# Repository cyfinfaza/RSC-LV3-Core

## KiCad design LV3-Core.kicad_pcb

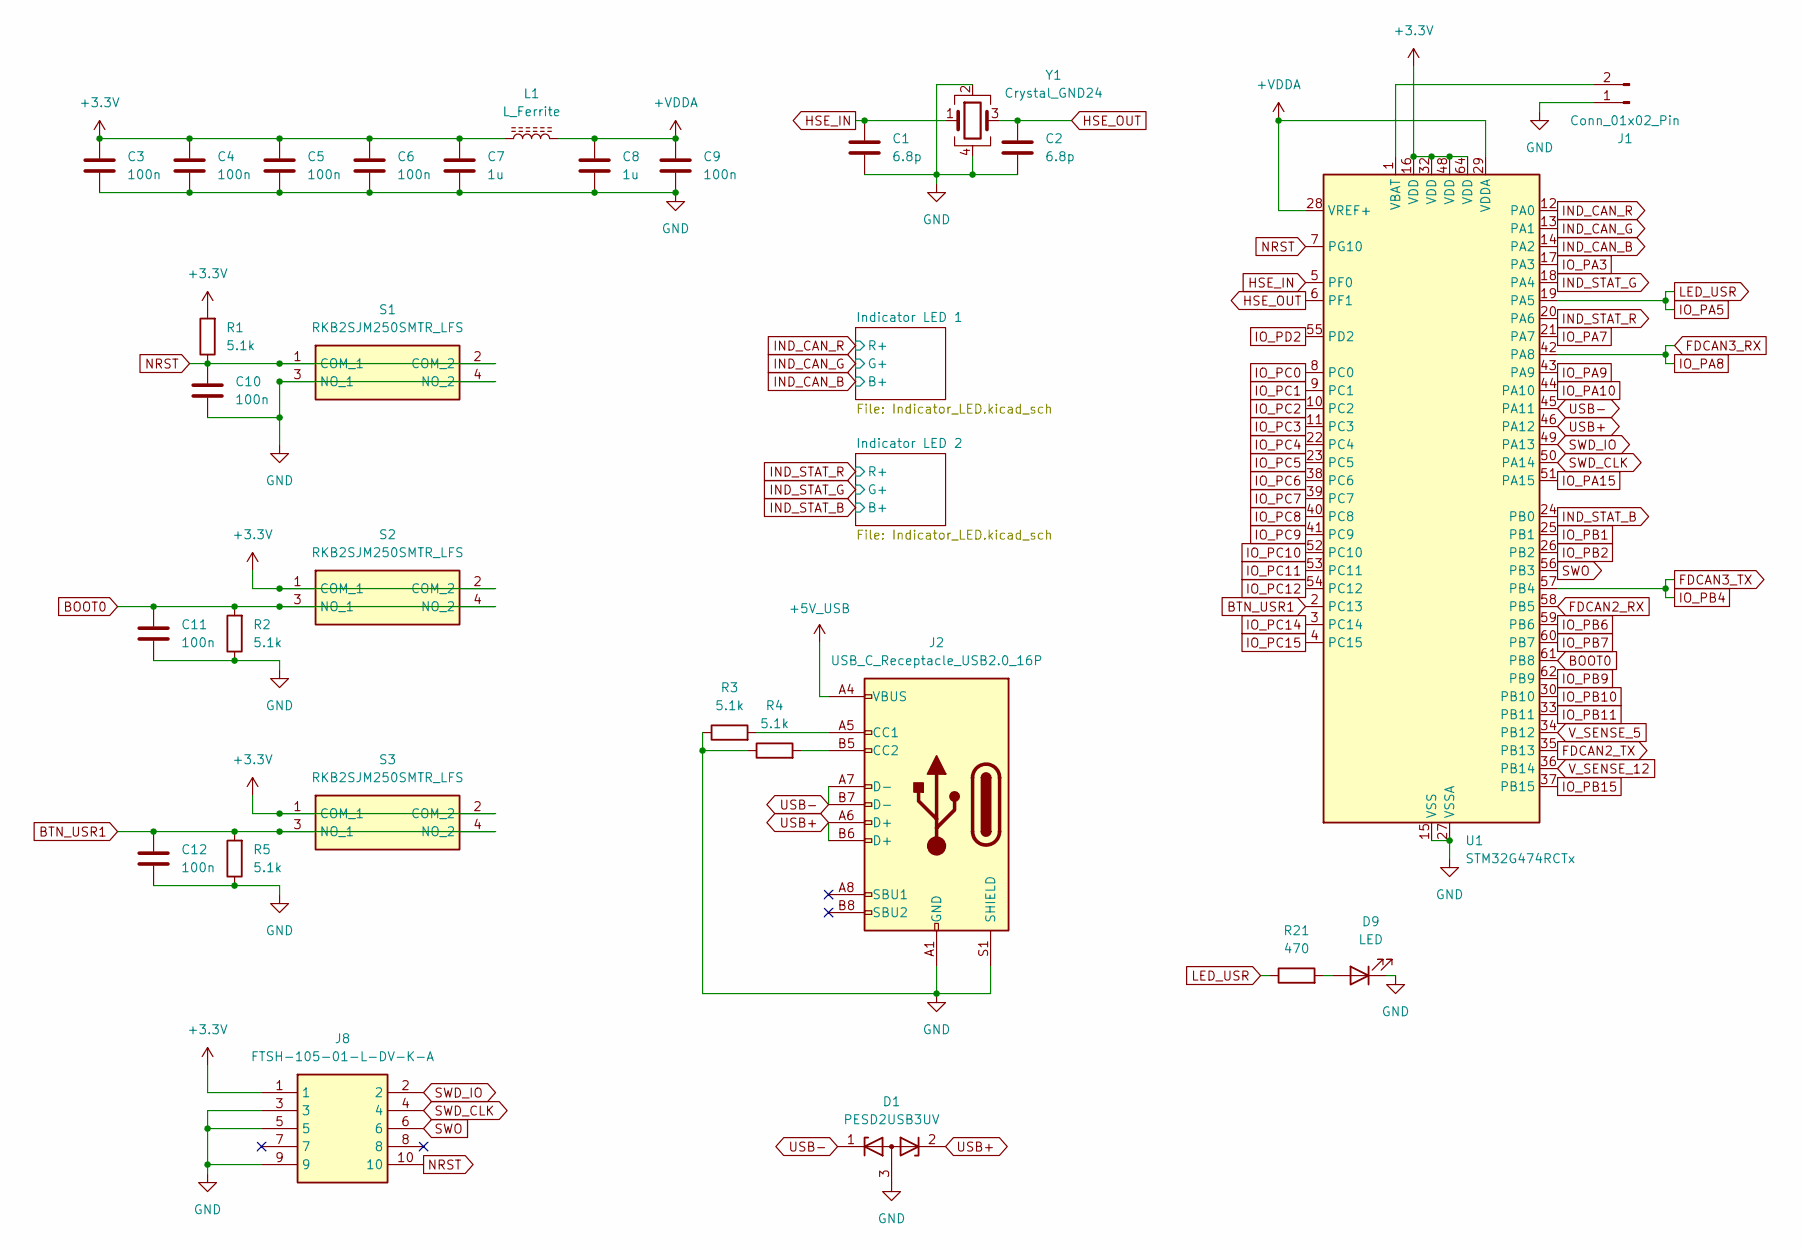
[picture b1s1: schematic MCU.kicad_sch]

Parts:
C1, C2: 6.8p; C_0603_1608Metric_Pad1.08x0.95mm_HandSolder
C3, C4, C5, C6, C9, C10, C11, C12: 100n; C_0603_1608Metric_Pad1.08x0.95mm_HandSolder
C7, C8: 1u; C_0603_1608Metric_Pad1.08x0.95mm_HandSolder
D1: PESD2USB3UV; SOT-23W
D9: LED; LED_0603_1608Metric_Pad1.05x0.95mm_HandSolder
J1: Conn_01x02_Pin; PinHeader_1x02_P2.54mm_Vertical
J2: USB_C_Receptacle_USB2.0_16P; USB_C_Receptacle_HRO_TYPE-C-31-M-12
J8: FTSH-105-01-L-DV-K-A; FTSH-105-XX-YYY-DV-K-A; Mouser Part Number 200-FTSH10501LDVKA
L1: L_Ferrite; L_0603_1608Metric_Pad1.05x0.95mm_HandSolder
R1, R2, R3, R4, R5: 5.1k; R_0603_1608Metric_Pad0.98x0.95mm_HandSolder
R21: 470; R_0603_1608Metric_Pad0.98x0.95mm_HandSolder
S1, S2, S3: RKB2SJM250SMTR_LFS; RKB2SJM250SMTRLFS; Mouser Part Number 611-RKB2SJM250SMTRLF
U1: STM32G474RCTx; LQFP-64_10x10mm_P0.5mm
Y1: Crystal_GND24; Crystal_SMD_3225-4Pin_3.2x2.5mm

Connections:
+3.3V: C3.1, C4.1, C5.1, C6.1, C7.1, J8.1, L1.1, R1.2, S2.1 (COM_1), S2.2 (COM_2), S3.1 (COM_1), S3.2 (COM_2), U1.16 (VDD), U1.32 (VDD), U1.48 (VDD), U1.64 (VDD); also elsewhere on the board
+5V_USB: J2.A4 (VBUS), J2.A9 (VBUS), J2.B4 (VBUS), J2.B9 (VBUS); also elsewhere on the board
+VDDA: C8.1, C9.1, L1.2, U1.28 (VREF+), U1.29 (VDDA)
BOOT0: C11.1, R2.2, S2.3 (NO_1), S2.4 (NO_2), U1.61 (PB8)
BTN_USR1: C12.1, R5.2, S3.3 (NO_1), S3.4 (NO_2), U1.2 (PC13)
FDCAN2_RX: U1.58 (PB5); also elsewhere on the board
FDCAN2_TX: U1.35 (PB13); also elsewhere on the board
FDCAN3_RX: U1.42 (PA8); also elsewhere on the board
FDCAN3_TX: U1.57 (PB4); also elsewhere on the board
GND: C1.2, C2.2, C3.2, C4.2, C5.2, C6.2, C7.2, C8.2, C9.2, C10.2, C11.2, C12.2, D1.3 (A), D9.1 (K), J1.1, J2.A1 (GND), J2.A12 (GND), J2.B1 (GND), J2.B12 (GND), J2.S1 (SHIELD), J8.3, J8.5, J8.9, R2.1, R3.1, R4.1, R5.1, S1.3 (NO_1), S1.4 (NO_2), U1.15 (VSS), U1.27 (VSSA), U1.31 (VSS), U1.47 (VSS), U1.63 (VSS), Y1.2, Y1.4; also elsewhere on the board
HSE_IN: C1.1, U1.5 (PF0), Y1.1
HSE_OUT: C2.1, U1.6 (PF1), Y1.3
IND_CAN_B: U1.14 (PA2); also elsewhere on the board
IND_CAN_G: U1.13 (PA1); also elsewhere on the board
IND_CAN_R: U1.12 (PA0); also elsewhere on the board
IND_STAT_B: U1.24 (PB0); also elsewhere on the board
IND_STAT_G: U1.18 (PA4); also elsewhere on the board
IND_STAT_R: U1.20 (PA6); also elsewhere on the board
IO_PA3: U1.17 (PA3); also elsewhere on the board
IO_PA5: R21.1, U1.19 (PA5); also elsewhere on the board
IO_PA7: U1.21 (PA7); also elsewhere on the board
IO_PA9: U1.43 (PA9); also elsewhere on the board
IO_PA10: U1.44 (PA10); also elsewhere on the board
IO_PA15: U1.51 (PA15); also elsewhere on the board
IO_PB1: U1.25 (PB1); also elsewhere on the board
IO_PB2: U1.26 (PB2); also elsewhere on the board
IO_PB6: U1.59 (PB6); also elsewhere on the board
IO_PB7: U1.60 (PB7); also elsewhere on the board
IO_PB9: U1.62 (PB9); also elsewhere on the board
IO_PB10: U1.30 (PB10); also elsewhere on the board
IO_PB11: U1.33 (PB11); also elsewhere on the board
IO_PB15: U1.37 (PB15); also elsewhere on the board
IO_PC0: U1.8 (PC0); also elsewhere on the board
IO_PC1: U1.9 (PC1); also elsewhere on the board
IO_PC2: U1.10 (PC2); also elsewhere on the board
IO_PC3: U1.11 (PC3); also elsewhere on the board
IO_PC4: U1.22 (PC4); also elsewhere on the board
IO_PC5: U1.23 (PC5); also elsewhere on the board
IO_PC6: U1.38 (PC6); also elsewhere on the board
IO_PC7: U1.39 (PC7); also elsewhere on the board
IO_PC8: U1.40 (PC8); also elsewhere on the board
IO_PC9: U1.41 (PC9); also elsewhere on the board
IO_PC10: U1.52 (PC10); also elsewhere on the board
IO_PC11: U1.53 (PC11); also elsewhere on the board
IO_PC12: U1.54 (PC12); also elsewhere on the board
IO_PC14: U1.3 (PC14); also elsewhere on the board
IO_PC15: U1.4 (PC15); also elsewhere on the board
IO_PD2: U1.55 (PD2); also elsewhere on the board
NRST: C10.1, J8.10, R1.1, S1.1 (COM_1), S1.2 (COM_2), U1.7 (PG10)
unnamed: D9.2 (A), R21.2
unnamed: J1.2, U1.1 (VBAT)
unnamed: J2.A5 (CC1), R3.2
unnamed: J2.B5 (CC2), R4.2
SWD_CLK: J8.4, U1.50 (PA14)
SWD_IO: J8.2, U1.49 (PA13)
SWO: J8.6, U1.56 (PB3)
USB+: D1.2 (K), J2.A6 (D+), J2.B6 (D+), U1.46 (PA12)
USB-: D1.1 (K), J2.A7 (D-), J2.B7 (D-), U1.45 (PA11)
V_SENSE_5: U1.34 (PB12); also elsewhere on the board
V_SENSE_12: U1.36 (PB14); also elsewhere on the board

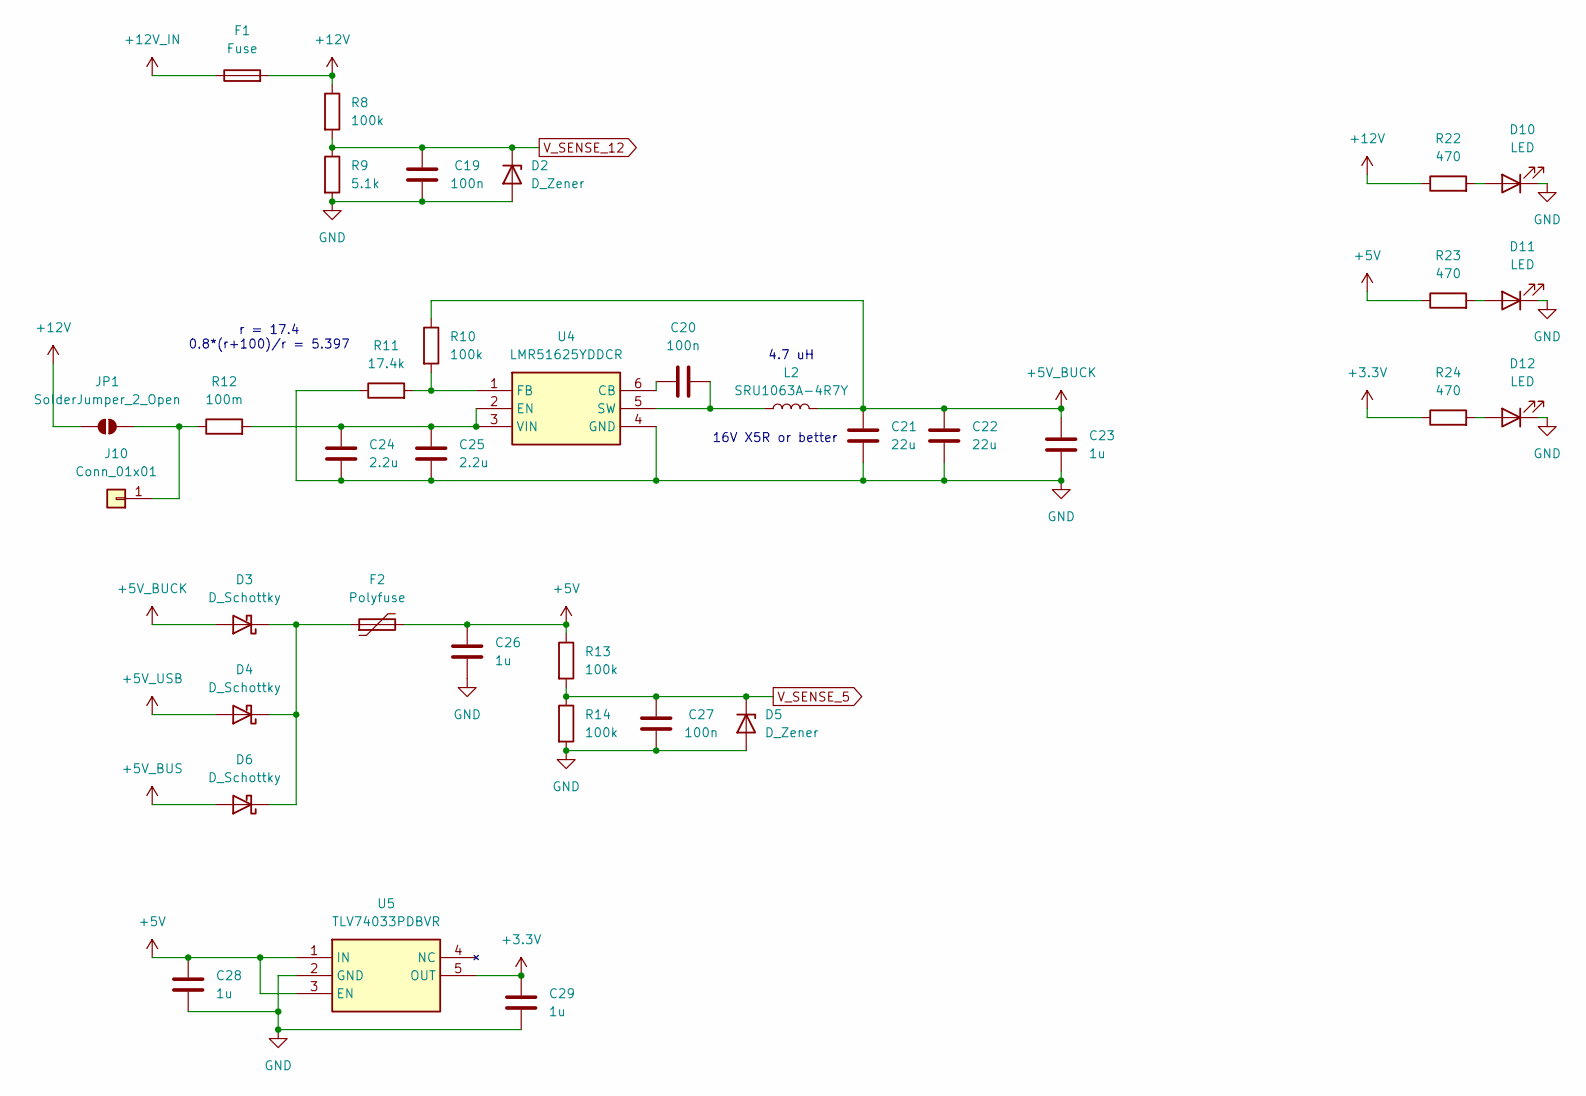
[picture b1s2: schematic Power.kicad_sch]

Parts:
C19, C20, C27: 100n; C_0603_1608Metric_Pad1.08x0.95mm_HandSolder
C21, C22: 22u; C_1206_3216Metric_Pad1.33x1.80mm_HandSolder
C23, C26, C28, C29: 1u; C_0603_1608Metric_Pad1.08x0.95mm_HandSolder
C24, C25: 2.2u; C_0603_1608Metric_Pad1.08x0.95mm_HandSolder
D2, D5: D_Zener; D_SOD-323_HandSoldering
D3, D4, D6: D_Schottky; D_SMA
D10, D11, D12: LED; LED_0603_1608Metric_Pad1.05x0.95mm_HandSolder
F1: Fuse; Fuseholder_Blade_Mini_Keystone_3568
F2: Polyfuse; Fuse_1812_4532Metric_Pad1.30x3.40mm_HandSolder
J10: Conn_01x01; PinHeader_1x01_P2.54mm_Vertical
JP1: SolderJumper_2_Open; SolderJumper-2_P1.3mm_Open_RoundedPad1.0x1.5mm
L2: SRU1063A-4R7Y; L_Bourns-SRU1028_10.0x10.0mm
R8, R10, R13, R14: 100k; R_0603_1608Metric_Pad0.98x0.95mm_HandSolder
R9: 5.1k; R_0603_1608Metric_Pad0.98x0.95mm_HandSolder
R11: 17.4k; R_0603_1608Metric_Pad0.98x0.95mm_HandSolder
R12: 100m; R_1206_3216Metric_Pad1.30x1.75mm_HandSolder
R22, R23, R24: 470; R_0603_1608Metric_Pad0.98x0.95mm_HandSolder
U4: LMR51625YDDCR; SOT95P280X110-6N; Manufacturer_Part_Number LMR51625YFDDCR; Mouser Part Number 595-LMR51625YFDDCR
U5: TLV74033PDBVR; SOT95P280X145-5N; Mouser Part Number 595-TLV74033PDBVR

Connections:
+3.3V: C29.1, R24.1, U5.5 (OUT); also elsewhere on the board
+5V: C26.1, C28.1, F2.2, R13.1, R23.1, U5.1 (IN), U5.3 (EN); also elsewhere on the board
+5V_BUCK: C21.1, C22.1, C23.1, D3.2 (A), L2.2, R10.1
+5V_BUS: D6.2 (A); also elsewhere on the board
+5V_USB: D4.2 (A); also elsewhere on the board
+12V: F1.2, JP1.1 (A), R8.1, R22.1; also elsewhere on the board
+12V_IN: F1.1; also elsewhere on the board
GND: C19.2, C21.2, C22.2, C23.2, C24.2, C25.2, C26.2, C27.2, C28.2, C29.2, D2.2 (A), D5.2 (A), D10.1 (K), D11.1 (K), D12.1 (K), R9.2, R11.1, R14.2, U4.4 (GND), U5.2 (GND); also elsewhere on the board
unnamed: D3.1 (K), D4.1 (K), D6.1 (K), F2.1
unnamed: D10.2 (A), R22.2
unnamed: D11.2 (A), R23.2
unnamed: D12.2 (A), R24.2
unnamed: C20.1, U4.6 (CB)
unnamed: C24.1, C25.1, R12.2, U4.2 (EN), U4.3 (VIN)
unnamed: R10.2, R11.2, U4.1 (FB)
unnamed: C20.2, L2.1, U4.5 (SW)
V_SENSE_5: C27.1, D5.1 (K), R13.2, R14.1; also elsewhere on the board
V_SENSE_12: C19.1, D2.1 (K), R8.2, R9.1; also elsewhere on the board

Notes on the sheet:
16V X5R or better
4.7 uH
r = 17.4 0.8*(r+100)/r = 5.397

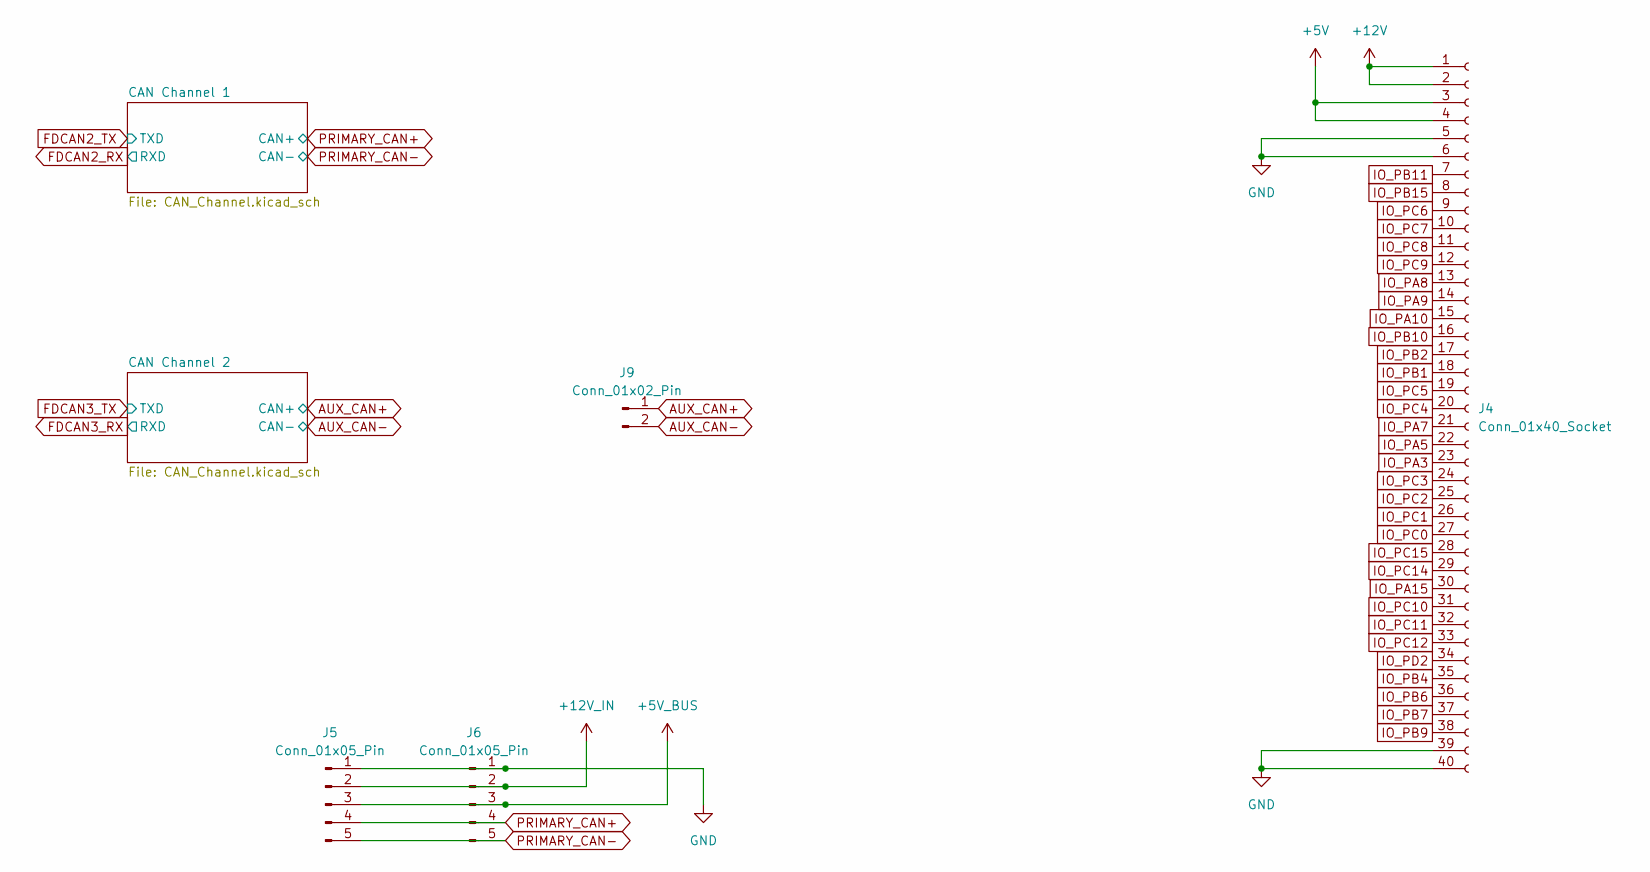
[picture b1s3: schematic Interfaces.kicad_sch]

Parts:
J4: Conn_01x40_Socket; PinSocket_1x40_P2.54mm_Horizontal
J5, J6: Conn_01x05_Pin; Molex_Micro-Fit_3.0_43650-0515_1x05_P3.00mm_Vertical
J9: Conn_01x02_Pin; Molex_Micro-Fit_3.0_43650-0215_1x02_P3.00mm_Vertical

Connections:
+5V: J4.3, J4.4; also elsewhere on the board
+5V_BUS: J5.3, J6.3; also elsewhere on the board
+12V: J4.1, J4.2; also elsewhere on the board
+12V_IN: J5.2, J6.2; also elsewhere on the board
AUX_CAN+: J9.1; also elsewhere on the board
AUX_CAN-: J9.2; also elsewhere on the board
FDCAN3_RX: J4.13; also elsewhere on the board
FDCAN3_TX: J4.35; also elsewhere on the board
GND: J4.5, J4.6, J4.39, J4.40, J5.1, J6.1; also elsewhere on the board
IO_PA3: J4.23; also elsewhere on the board
IO_PA5: J4.22; also elsewhere on the board
IO_PA7: J4.21; also elsewhere on the board
IO_PA9: J4.14; also elsewhere on the board
IO_PA10: J4.15; also elsewhere on the board
IO_PA15: J4.30; also elsewhere on the board
IO_PB1: J4.18; also elsewhere on the board
IO_PB2: J4.17; also elsewhere on the board
IO_PB6: J4.36; also elsewhere on the board
IO_PB7: J4.37; also elsewhere on the board
IO_PB9: J4.38; also elsewhere on the board
IO_PB10: J4.16; also elsewhere on the board
IO_PB11: J4.7; also elsewhere on the board
IO_PB15: J4.8; also elsewhere on the board
IO_PC0: J4.27; also elsewhere on the board
IO_PC1: J4.26; also elsewhere on the board
IO_PC2: J4.25; also elsewhere on the board
IO_PC3: J4.24; also elsewhere on the board
IO_PC4: J4.20; also elsewhere on the board
IO_PC5: J4.19; also elsewhere on the board
IO_PC6: J4.9; also elsewhere on the board
IO_PC7: J4.10; also elsewhere on the board
IO_PC8: J4.11; also elsewhere on the board
IO_PC9: J4.12; also elsewhere on the board
IO_PC10: J4.31; also elsewhere on the board
IO_PC11: J4.32; also elsewhere on the board
IO_PC12: J4.33; also elsewhere on the board
IO_PC14: J4.29; also elsewhere on the board
IO_PC15: J4.28; also elsewhere on the board
IO_PD2: J4.34; also elsewhere on the board
PRIMARY_CAN+: J5.4, J6.4; also elsewhere on the board
PRIMARY_CAN-: J5.5, J6.5; also elsewhere on the board

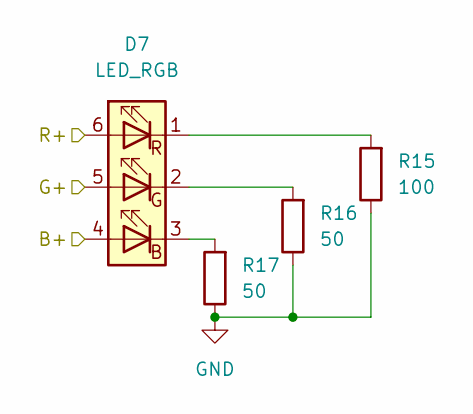
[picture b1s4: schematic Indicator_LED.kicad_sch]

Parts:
D7: LED_RGB; LED_RGB_5050-6
R15: 100; R_0603_1608Metric_Pad0.98x0.95mm_HandSolder
R16, R17: 50; R_0603_1608Metric_Pad0.98x0.95mm_HandSolder

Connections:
GND: R15.1, R16.1, R17.1; also elsewhere on the board
IND_CAN_B: D7.4 (BA); also elsewhere on the board
IND_CAN_G: D7.5 (GA); also elsewhere on the board
IND_CAN_R: D7.6 (RA); also elsewhere on the board
unnamed: D7.3 (BK), R17.2
unnamed: D7.2 (GK), R16.2
unnamed: D7.1 (RK), R15.2

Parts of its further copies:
D8: LED_RGB; LED_RGB_5050-6
R19, R20: 50; R_0603_1608Metric_Pad0.98x0.95mm_HandSolder

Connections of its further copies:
GND: R19.1, R20.1; also elsewhere on the board
IND_STAT_B: D8.4 (BA); also elsewhere on the board
IND_STAT_G: D8.5 (GA); also elsewhere on the board
IND_STAT_R: D8.6 (RA); also elsewhere on the board
unnamed: D8.3 (BK), R20.2
unnamed: D8.2 (GK), R19.2
unnamed 62: D8.1 (RK); also elsewhere on the board

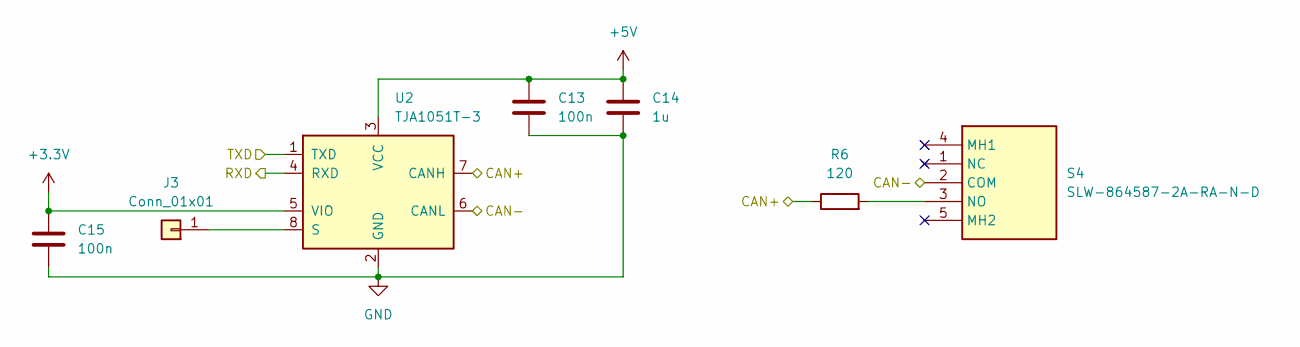
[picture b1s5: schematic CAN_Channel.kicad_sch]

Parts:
C13, C15: 100n; C_0603_1608Metric_Pad1.08x0.95mm_HandSolder
C14: 1u; C_0603_1608Metric_Pad1.08x0.95mm_HandSolder
J3: Conn_01x01; PinHeader_1x01_P2.54mm_Vertical
R6: 120; R_0603_1608Metric_Pad0.98x0.95mm_HandSolder
S4: SLW-864587-2A-RA-N-D; SLW8645872ARAND; Mouser Part Number 179-SLW8645872ARAND
U2: TJA1051T-3; SOIC-8_3.9x4.9mm_P1.27mm

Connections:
+3.3V: C15.1, U2.5 (VIO); also elsewhere on the board
+5V: C13.1, C14.1, U2.3 (VCC); also elsewhere on the board
FDCAN2_RX: U2.4 (RXD); also elsewhere on the board
FDCAN2_TX: U2.1 (TXD); also elsewhere on the board
GND: C13.2, C14.2, C15.2, U2.2 (GND); also elsewhere on the board
unnamed: J3.1, U2.8 (S)
unnamed: R6.2, S4.3 (NO)
PRIMARY_CAN+: R6.1, U2.7 (CANH); also elsewhere on the board
PRIMARY_CAN-: S4.2 (COM), U2.6 (CANL); also elsewhere on the board

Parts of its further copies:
C16, C18: 100n; C_0603_1608Metric_Pad1.08x0.95mm_HandSolder
C17: 1u; C_0603_1608Metric_Pad1.08x0.95mm_HandSolder
J7: Conn_01x01; PinHeader_1x01_P2.54mm_Vertical
R7: 120; R_0603_1608Metric_Pad0.98x0.95mm_HandSolder
S5: SLW-864587-2A-RA-N-D; SLW8645872ARAND; Mouser Part Number 179-SLW8645872ARAND
U3: TJA1051T-3; SOIC-8_3.9x4.9mm_P1.27mm

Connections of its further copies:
+3.3V: C18.1, U3.5 (VIO); also elsewhere on the board
+5V: C16.1, C17.1, U3.3 (VCC); also elsewhere on the board
AUX_CAN+: R7.1, U3.7 (CANH); also elsewhere on the board
AUX_CAN-: S5.2 (COM), U3.6 (CANL); also elsewhere on the board
FDCAN3_RX: U3.4 (RXD); also elsewhere on the board
FDCAN3_TX: U3.1 (TXD); also elsewhere on the board
GND: C16.2, C17.2, C18.2, U3.2 (GND); also elsewhere on the board
unnamed: J7.1, U3.8 (S)
unnamed: R7.2, S5.3 (NO)

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
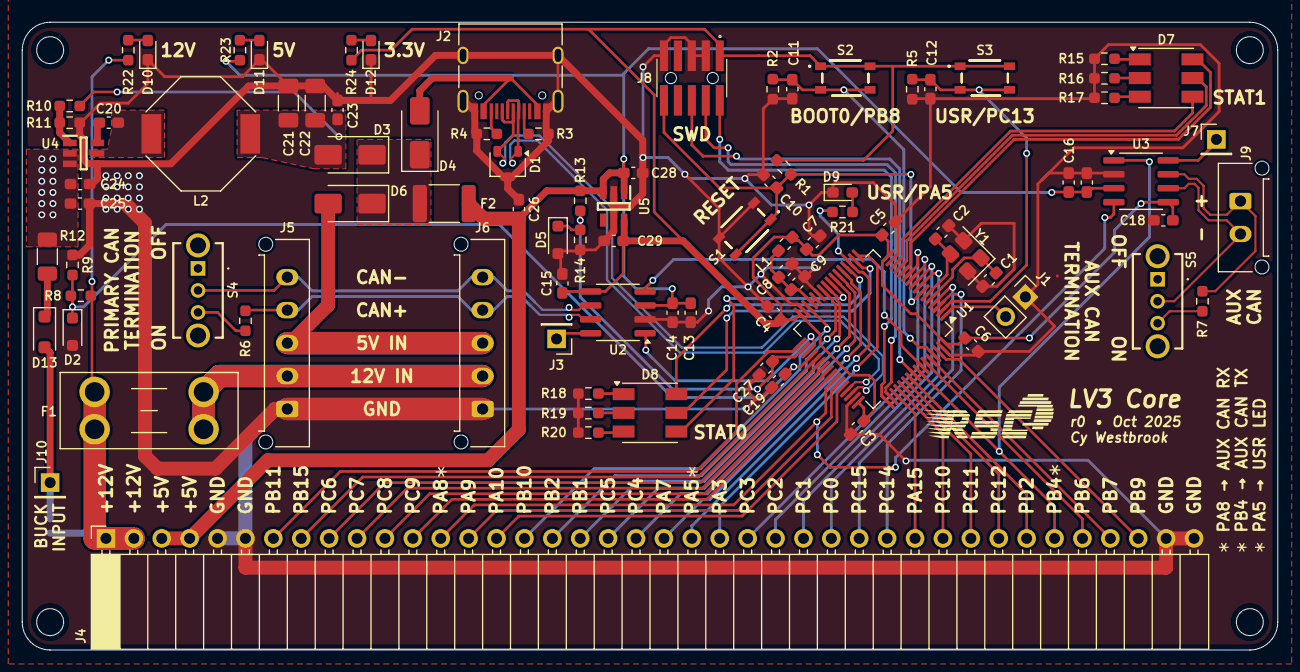
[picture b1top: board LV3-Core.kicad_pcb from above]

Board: 2 copper layers, 114.3 x 57.2 mm, 92 parts (1 on the bottom side), 89 nets.

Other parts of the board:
D13: D_Schottky; D_SOD-123F
R18: 120; R_0603_1608Metric_Pad0.98x0.95mm_HandSolder

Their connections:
GND: R18.1; also elsewhere on the board
unnamed 62: R18.2; also elsewhere on the board

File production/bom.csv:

Designator,Footprint,Quantity,Value,LCSC Part #
"C1, C2",0603,2,6.8p,
"C10, C11, C12, C13, C15, C16, C18, C19, C20, C27, C3, C4, C5, C6, C9",0603,15,100n,
"C14, C17, C23, C26, C28, C29, C7, C8",0603,8,1u,
"C21, C22",1206,2,22u,
"C24, C25",0603,2,2.2u,
D1,SOT-23W,1,PESD2USB3UV,
"D10, D11, D12, D9",0603,4,LED,
D13,D_SOD-123F,1,D_Schottky,
"D2, D5",D_SOD-323_HandSoldering,2,D_Zener,
"D3, D4, D6",D_SMA,3,D_Schottky,
"D7, D8",LED_RGB_5050-6,2,LED_RGB,
F1,Fuseholder_Blade_Mini_Keystone_3568,1,Fuse,
F2,1812,1,Polyfuse,
J1,PinHeader_1x02_P2.54mm_Vertical,1,Conn_01x02_Pin,
"J10, J3, J7",PinHeader_1x01_P2.54mm_Vertical,3,Conn_01x01,
J2,USB_C_Receptacle_HRO_TYPE-C-31-M-12,1,USB_C_Receptacle_USB2.0_16P,
J4,PinSocket_1x40_P2.54mm_Horizontal,1,Conn_01x40_Socket,
"J5, J6",Molex_Micro-Fit_3.0_43650-0515_1x05_P3.00mm_Vertical,2,Conn_01x05_Pin,
J8,FTSH-105-XX-YYY-DV-K-A,1,FTSH-105-01-L-DV-K-A,
J9,Molex_Micro-Fit_3.0_43650-0215_1x02_P3.00mm_Vertical,1,Conn_01x02_Pin,
L1,0603,1,L_Ferrite,
L2,L_Bourns-SRU1028_10.0x10.0mm,1,SRU1063A-4R7Y,
"R1, R2, R3, R4, R5, R9",0603,6,5.1k,
"R10, R13, R14, R8",0603,4,100k,
R11,0603,1,17.4k,
R12,1206,1,100m,
"R15, R18, R24, R6, R7",0603,5,120,
"R16, R17, R19, R20",0603,4,50,
"R21, R23",0603,2,470,
R22,0603,1,2.2k,
"S1, S2, S3",RKB2SJM250SMTRLFS,3,RKB2SJM250SMTR_LFS,
"S4, S5",SLW8645872ARAND,2,SLW-864587-2A-RA-N-D,
U1,LQFP-64_10x10mm_P0.5mm,1,STM32G474RCTx,
"U2, U3",SOIC-8_3.9x4.9mm_P1.27mm,2,TJA1051T-3,
U4,SOT95P280X110-6N,1,LMR51625YDDCR,
U5,SOT95P280X145-5N,1,TLV74033PDBVR,
Y1,Crystal_SMD_3225-4Pin_3.2x2.5mm,1,Crystal_GND24,

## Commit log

2025-09-30 add power, some mcu components
2025-10-09 complete schematic, initial board layout
2025-10-12 layout almost complete
2025-10-13 completed layout and routing
2025-10-16 adjusted input power section, completed silkscreen text
2025-10-21 move aux can termination switch to make room for silkscreen
2025-10-23 minor silkscreen changes, add reverse block diode for 12v ORDER 23 october 2025
